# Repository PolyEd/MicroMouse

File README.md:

Hello! This is the central readme for the PolyEd MicroMouse Project. \
This file is a compilation of general (non-code specific) information relating to the project.

Our inspiration: \
[The Fastest Maze-Solving Competition On Earth](https://www.youtube.com/watch?v=ZMQbHMgK2rw)

The conference we will attend: \
[APEC](https://apec-conf.org/)

Rules:
- [The conference rules](https://s3.us-east-1.amazonaws.com/apec-conf-images/APEC_Policies_And_Procedures_Rev_7-3_2022-09-02.pdf) —\
  See page 15 "Minimum Age Policy" which implies there is no minimum age for the MicroMouse contest.
- [An old set of MicroMouse rules (revision 2009)](http://micromouseusa.com/wp-content/uploads/2013/10/APEC-Rules.pdf)

**Important** files to read before working with the Arduino code or using it:
- [I2C README](I2C-README.md)
- [Info about the plotting library used in this project](PLOTTER-README.md)

<!--
---
Also [Nim](https://nim-lang.org/) 😃
--><!--I (Joshua) commented this out to not be beligerent, please leave it in here in this form though, just for fun-->

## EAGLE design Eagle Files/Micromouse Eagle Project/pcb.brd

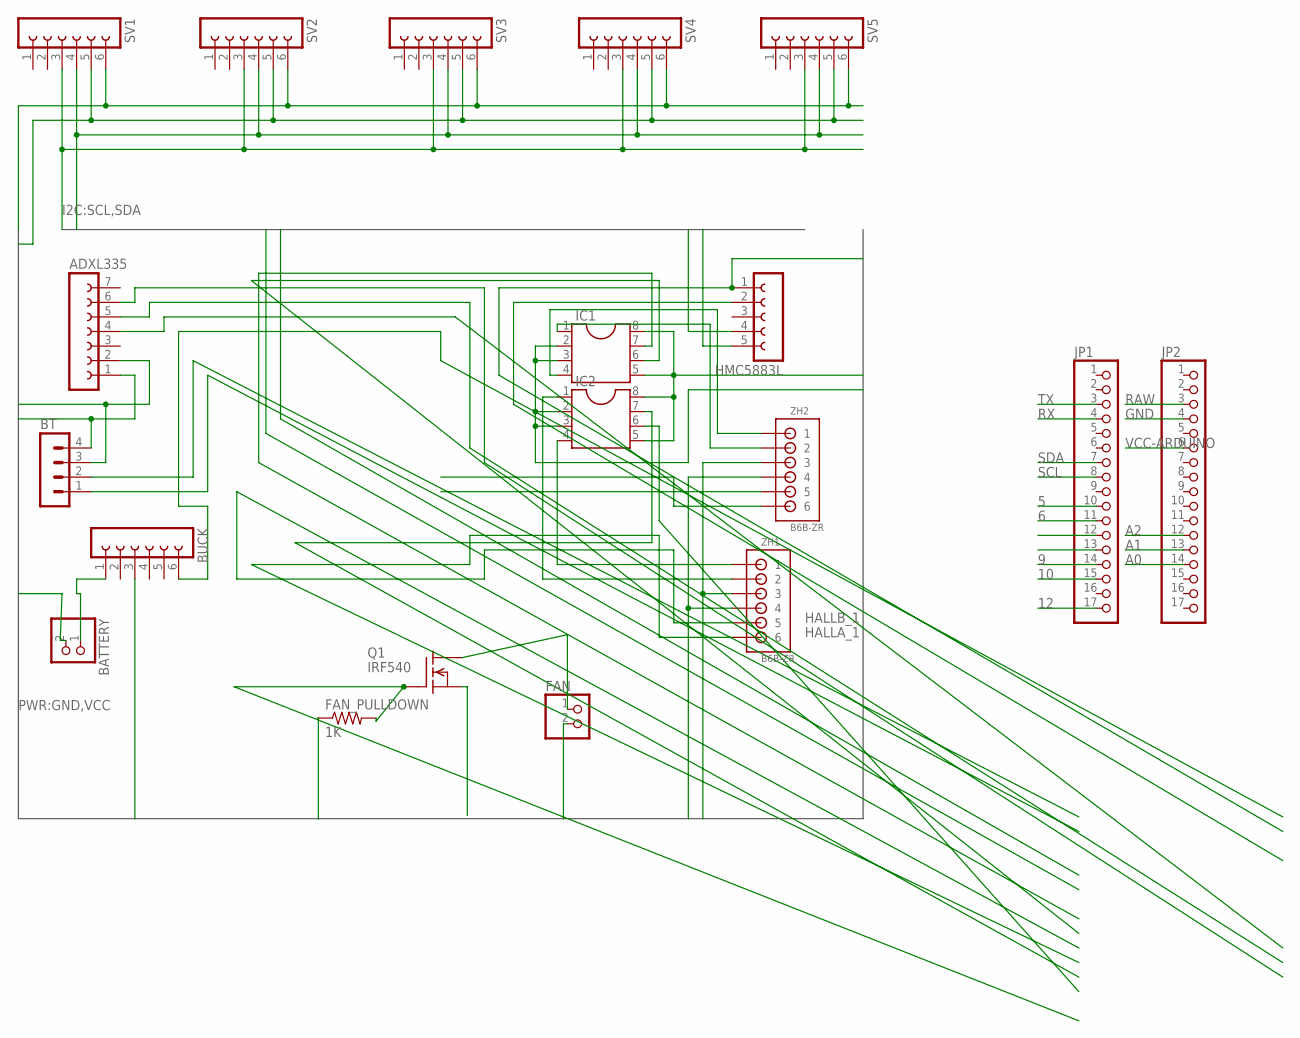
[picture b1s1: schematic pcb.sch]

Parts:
ADXL335: FE07-1; FE07
BATTERY: PINHD-1X2; 1X02
BT: MA04-1
BUCK: FE06-1; FE06
FAN: PINHD-1X2; 1X02
FAN_PULLDOWN: 1K; 0207/10
HMC5883L: FE05-1
IC1, IC2: DIL8S; SOCKET-08
JP1, JP2: PINHD-1X17; 1X17
Q1: IRF540; TO220
SV1, SV2, SV3, SV4, SV5: FE06-1; FE06
ZH1, ZH2: B6B-ZR

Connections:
5: IC1.7, JP1.10
6: IC1.6, JP1.11
9: IC2.7, JP1.14
10: IC2.6, JP1.15
12: FAN_PULLDOWN.2, JP1.17, Q1.1 (G)
A0: ADXL335.6, JP2.14
A1: ADXL335.5, JP2.13
A2: ADXL335.4, JP2.12
GND: ADXL335.2, BATTERY.2, BT.3, BUCK.3, FAN_PULLDOWN.1, HMC5883L.1, IC1.5, IC1.8, IC2.5, IC2.8, JP2.4, Q1.3 (S), SV1.5, SV2.5, SV3.5, SV4.5, SV5.5, ZH1.4, ZH2.4
HALLA_1: JP1.13, ZH1.6
HALLB_1: JP1.12, ZH1.5
unnamed: BATTERY.1, BUCK.1
unnamed: IC1.1, ZH2.2
unnamed: IC1.4, ZH2.1
unnamed: IC2.4, ZH1.1
unnamed: IC2.1, ZH1.2
unnamed: FAN.1, Q1.2 (D)
RAW: BUCK.6, JP2.3
RX: BT.1, JP1.4
SCL: HMC5883L.4, JP1.8, SV1.4, SV2.4, SV3.4, SV4.4, SV5.4
SDA: HMC5883L.5, JP1.7, SV1.3, SV2.3, SV3.3, SV4.3, SV5.3
TX: BT.2, JP1.3
VCC: ADXL335.1, BT.4, FAN.2, IC1.2, IC1.3, IC2.2, IC2.3, SV1.6, SV2.6, SV3.6, SV4.6, SV5.6, ZH1.3, ZH2.3
VCC-ARDUINO: HMC5883L.2, JP2.6

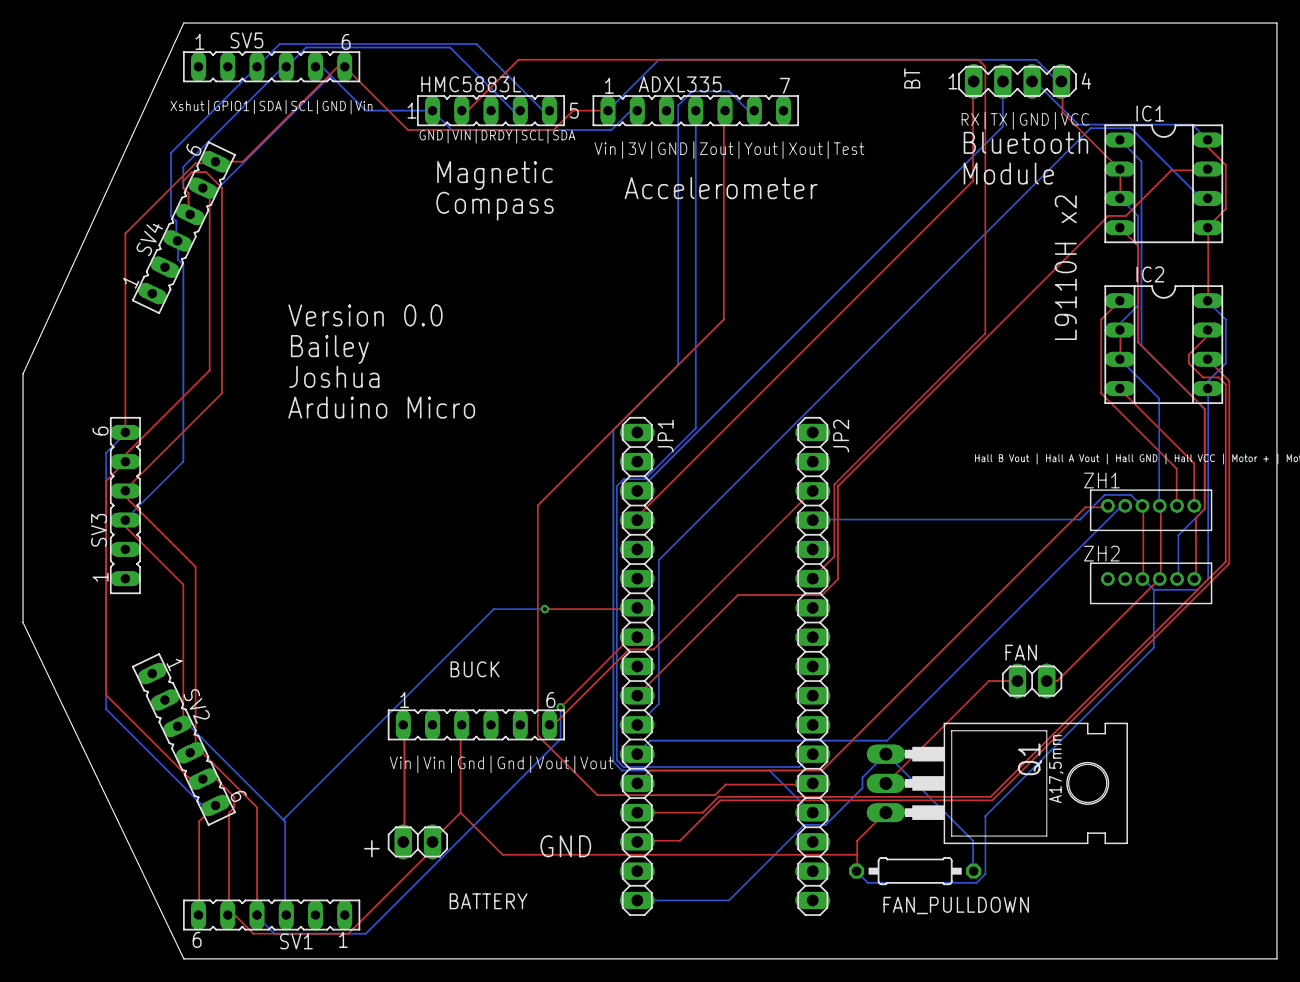
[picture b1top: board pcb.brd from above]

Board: 2 copper layers, 108.9 x 81.3 mm, 19 parts (0 on the bottom side), 24 nets.

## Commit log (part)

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2023-09-01 Update main.c
    now it has a main function
2023-09-01 Create README.txt
    added initial setup
2023-09-01 Create makefile
2023-09-01 Update makefile
2023-09-01 Fix up makefile
2023-09-04 Update README.txt
    added a space
2023-09-14 Create Arduino Uno Rev3 folder
2023-09-14 Add eagle files + schematics + other info
2023-09-14 Update README.txt
    added old ruleset
2023-09-14 A bunch of files for micromouse related projects
2023-09-16 Create old micromouse
2023-09-21 Added info about HMC5883
2023-09-22 Cleaned up README.md
    - Changed to use proper Markdown formatting for links
    - Removed the unnecessary and excessively-used `<br>`s and replaced them with `\`s at the end of lines to follow standard practice and to improve readability of Markdown source
    - Changed the writing to be more concise.
2023-09-25 Clarify some instructions and fix MD syntax
2023-09-29 Added ADXL335 info
2023-09-29 Move README for ADXL335 to correct directory
2023-10-11 Added info on I2C, plotting, and the VL53L0X.
2023-10-12 Update README.md to fix typo
2023-10-12 Add plotter code for ADXL335
2023-10-26 Added Pro Micro Eagle File
2023-10-26 Add N20 Gear Motor Connector Eagle File
2023-10-26 Changed Structure
2023-10-28 Added datasheets
2023-10-28 Create floodFillInC
2024-01-20 Update Eagle Design
2024-02-09 added labels
2024-10-24 thingamajig
2024-10-25 add try catch
2024-11-08 gtgt6gt6
    tvtgtygvgyguyygugy
2025-01-17 Reorganize file structure
2025-04-24 Add Disambiguation for some code and fix bug in microsuite noble
2025-05-29 add straight code (current version)
